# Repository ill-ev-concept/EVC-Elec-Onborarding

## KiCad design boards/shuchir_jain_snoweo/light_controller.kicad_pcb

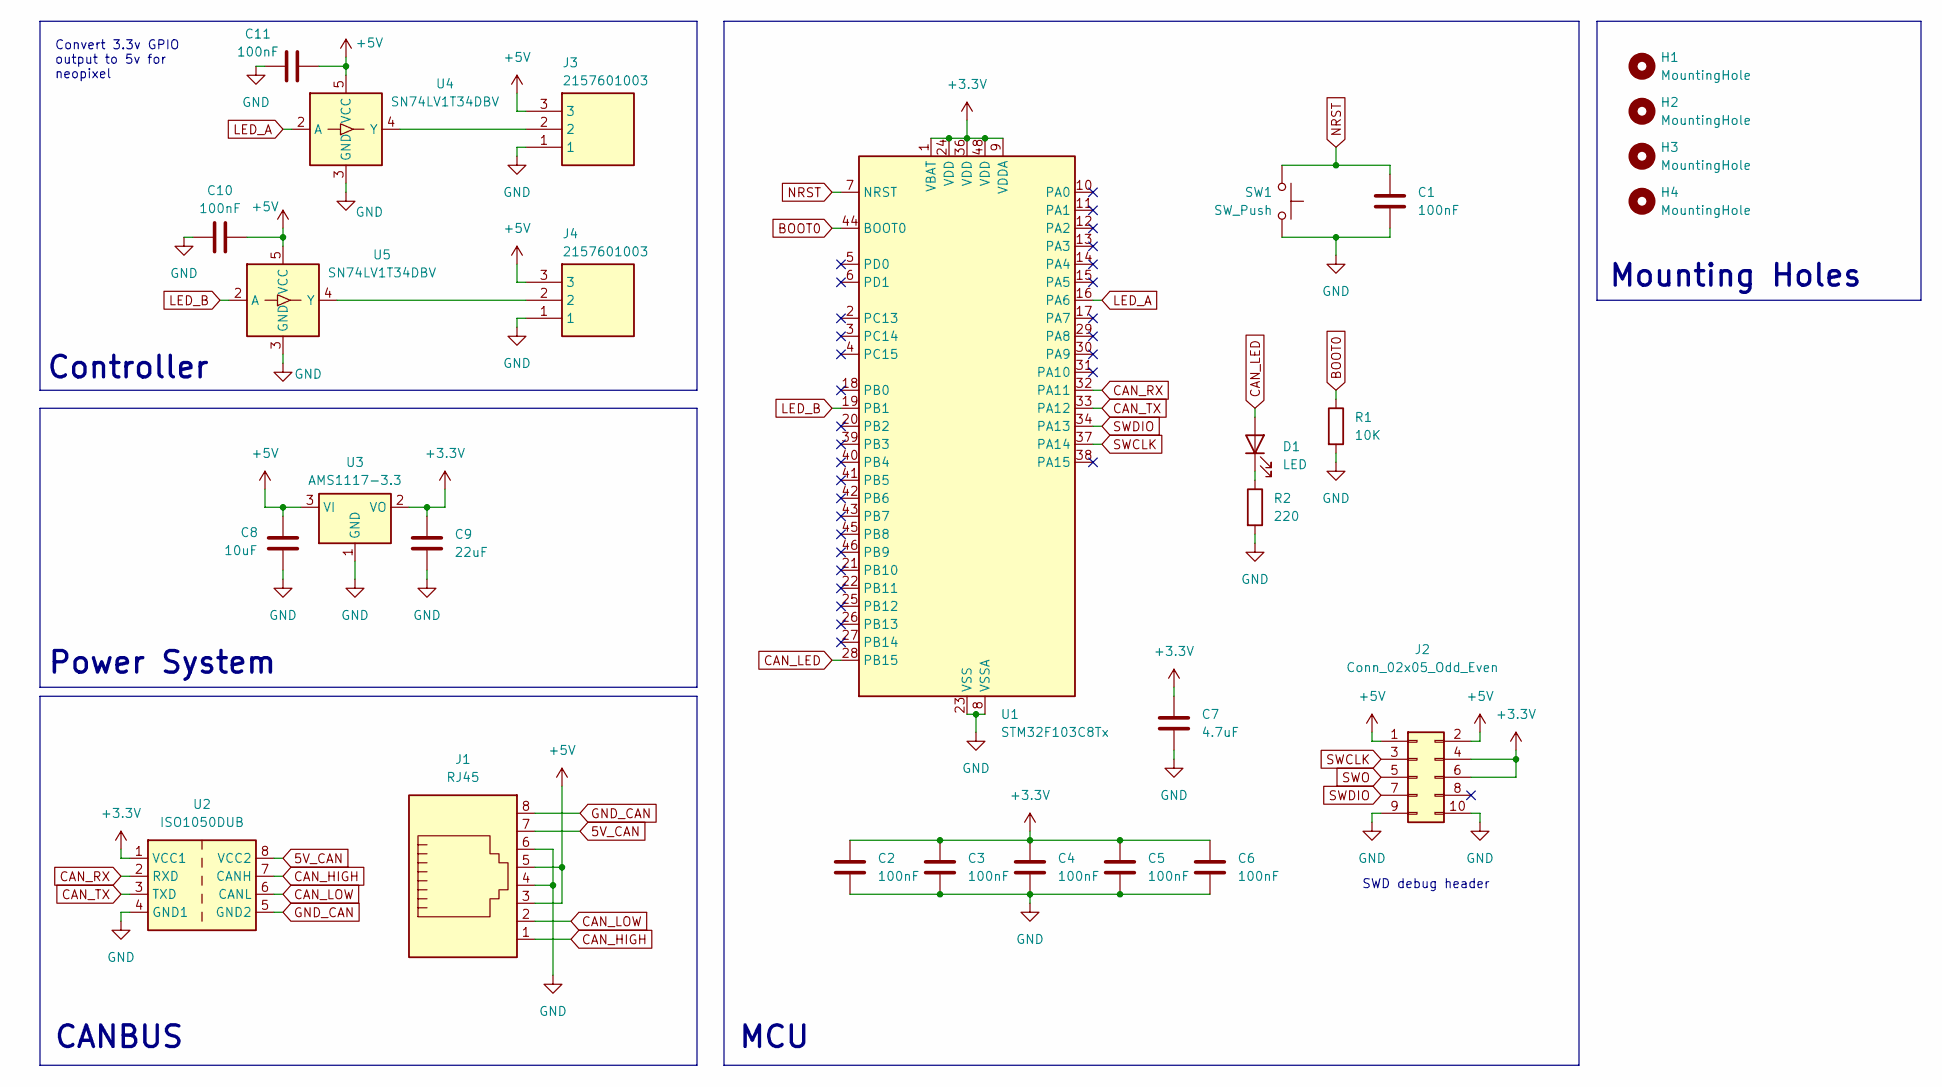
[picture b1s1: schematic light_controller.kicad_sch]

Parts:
C1, C2, C3, C4, C5, C6, C10, C11: 100nF; C_0805_2012Metric
C7: 4.7uF; C_0805_2012Metric
C8: 10uF; C_0805_2012Metric
C9: 22uF; C_0805_2012Metric
D1: LED; LED_0805_2012Metric
H1, H2, H3, H4: MountingHole; MountingHole_3.2mm_M3
J1: RJ45; RJ45_BEL_SS74301-00x_Vertical
J2: Conn_02x05_Odd_Even; PinHeader_2x05_P2.54mm_Vertical_SMD
J3, J4: 2157601003; 215760YY03; Manufacturer_Part_Number 2157601003
R1: 10K; R_0805_2012Metric
R2: 220; R_0805_2012Metric
SW1: SW_Push; SW_SPST_EVQQ2
U1: STM32F103C8Tx; LQFP-48_7x7mm_P0.5mm
U2: ISO1050DUB; SOP-8_6.62x9.15mm_P2.54mm
U3: AMS1117-3.3; SOT-223-3_TabPin2
U4, U5: SN74LV1T34DBV; SOT-23-5

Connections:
5V_CAN: J1.7, U2.8 (VCC2)
+3.3V: C2.1, C3.1, C4.1, C5.1, C6.1, C7.1, C9.1, J2.4, J2.6, U1.1 (VBAT), U1.9 (VDDA), U1.24 (VDD), U1.36 (VDD), U1.48 (VDD), U2.1 (VCC1), U3.2 (VO)
+5V: C8.1, C10.2, C11.2, J1.3, J1.5, J2.1, J2.2, J3.3, J4.3, U3.3 (VI), U4.5 (VCC), U5.5 (VCC)
BOOT0: R1.1, U1.44 (BOOT0)
CAN_HIGH: J1.1, U2.7 (CANH)
CAN_LED: D1.2 (A), U1.28 (PB15)
CAN_LOW: J1.2, U2.6 (CANL)
CAN_RX: U1.32 (PA11), U2.2 (RXD)
CAN_TX: U1.33 (PA12), U2.3 (TXD)
GND: C1.2, C2.2, C3.2, C4.2, C5.2, C6.2, C7.2, C8.2, C9.2, C10.1, C11.1, J1.4, J1.6, J2.9, J2.10, J3.1, J4.1, R1.2, R2.2, SW1.1, U1.8 (VSSA), U1.23 (VSS), U1.35 (VSS), U1.47 (VSS), U2.4 (GND1), U3.1 (GND), U4.3 (GND), U5.3 (GND)
GND_CAN: J1.8, U2.5 (GND2)
LED_A: U1.16 (PA6), U4.2 (A)
LED_B: U1.19 (PB1), U5.2 (A)
NRST: C1.1, SW1.2, U1.7 (NRST)
unnamed: D1.1 (K), R2.1
unnamed: J3.2, U4.4 (Y)
unnamed: J4.2, U5.4 (Y)
SWCLK: J2.3, U1.37 (PA14)
SWDIO: J2.7, U1.34 (PA13)
SWO: J2.5

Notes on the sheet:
Convert 3.3v GPIO output to 5v for neopixel
Power System
Mounting Holes
MCU
SWD debug header
CANBUS
Controller

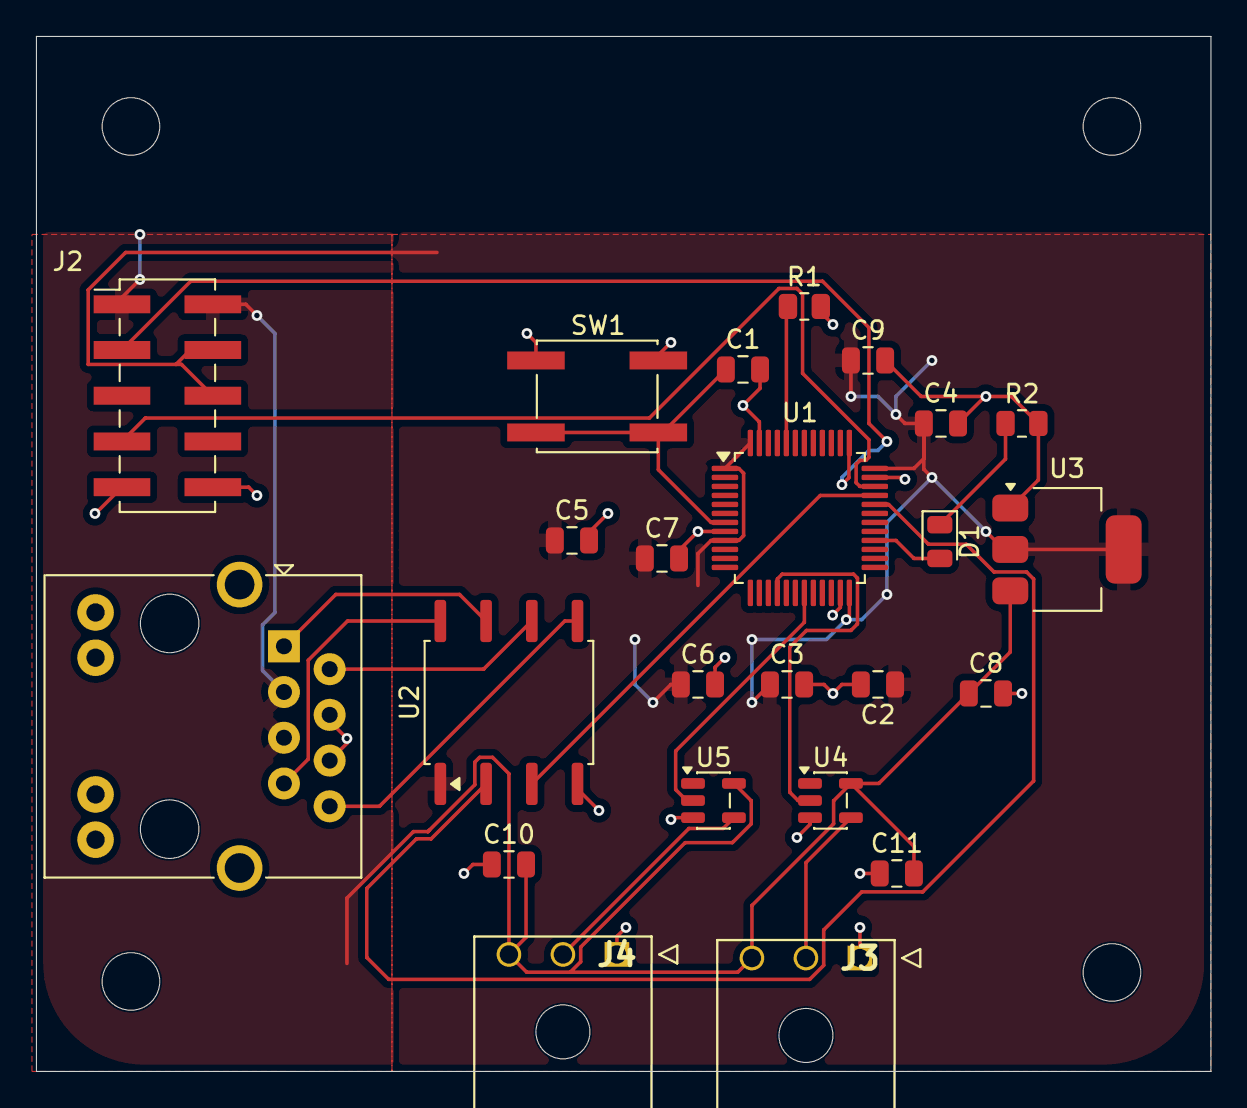
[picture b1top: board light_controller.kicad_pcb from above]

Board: 2 copper layers, 65.2 x 57.5 mm, 28 parts (0 on the bottom side), 19 nets.

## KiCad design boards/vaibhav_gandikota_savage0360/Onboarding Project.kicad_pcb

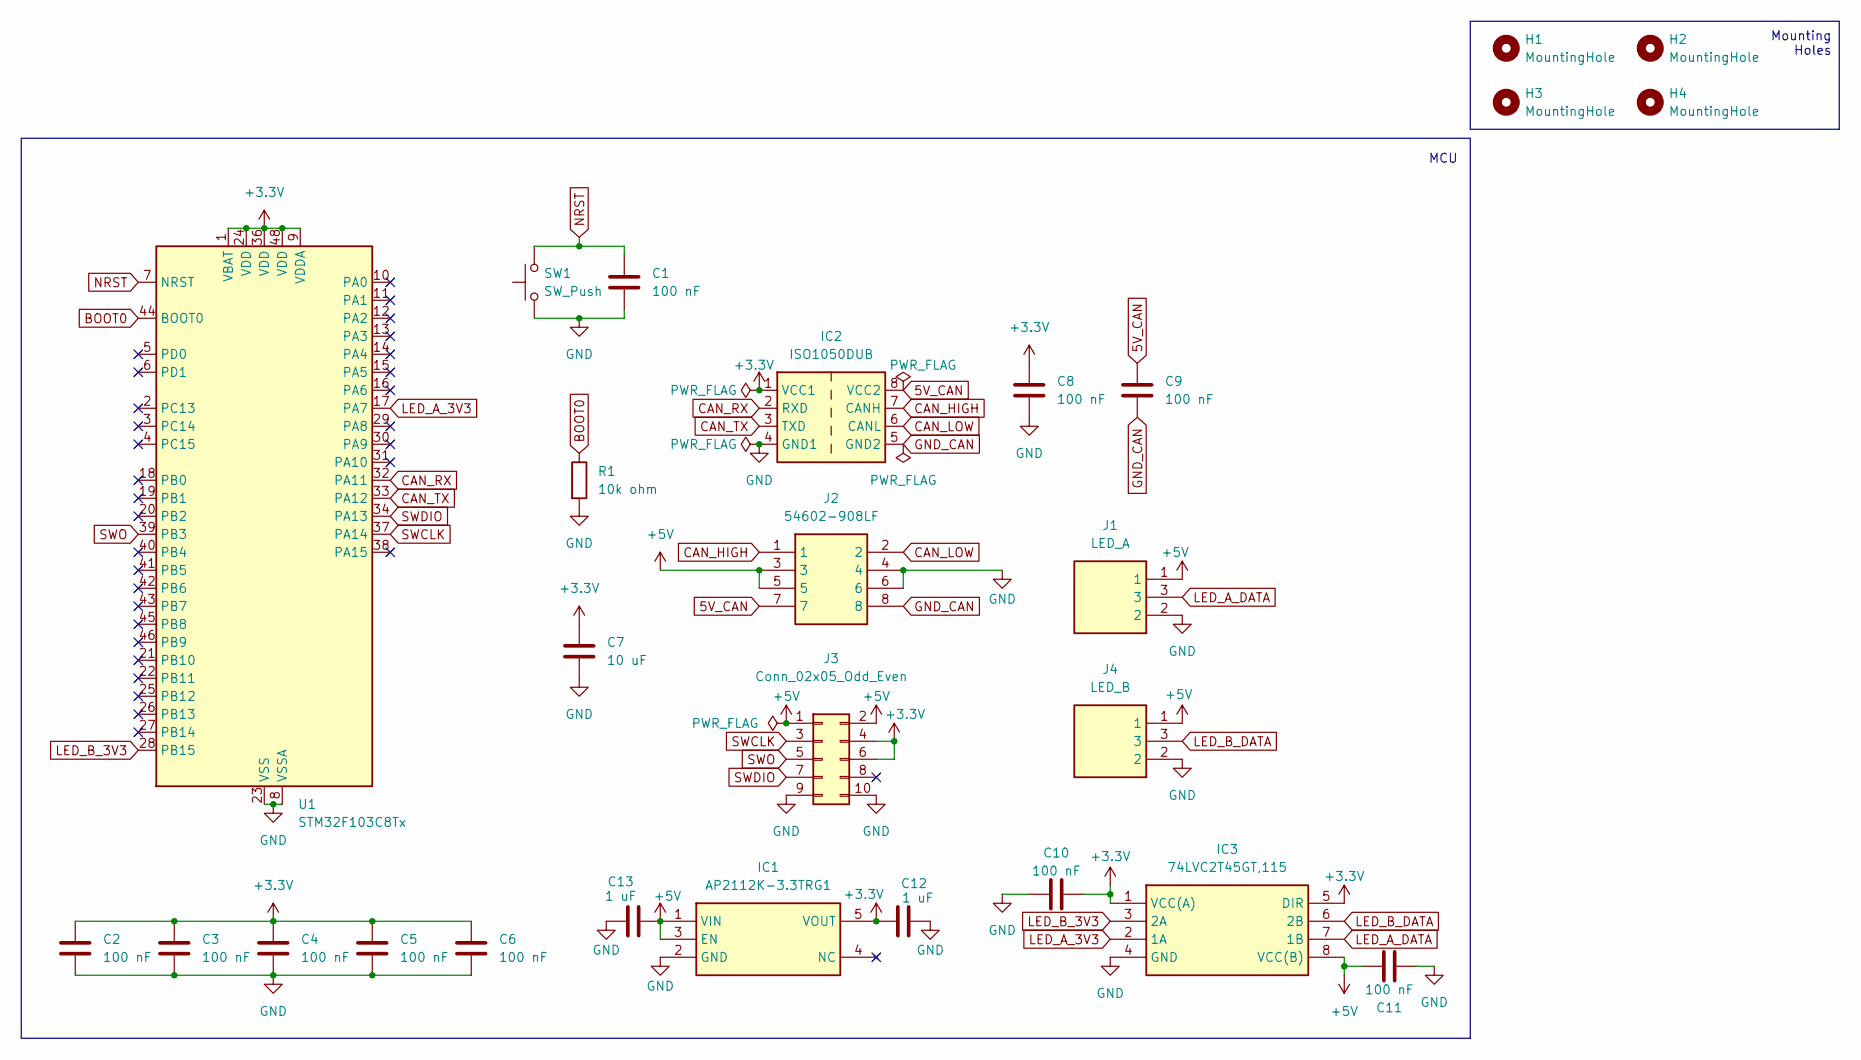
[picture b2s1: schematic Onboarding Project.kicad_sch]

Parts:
C1, C2, C3, C4, C5, C6, C8, C9, C10, C11: 100 nF; C_0805_2012Metric
C7: 10 uF; C_0805_2012Metric
C12, C13: 1 uF; C_0805_2012Metric
H1, H2, H3, H4: MountingHole; MountingHole_4.3mm_M4
IC1: AP2112K-3.3TRG1; SOT95P285X140-5N; Manufacturer_Part_Number AP2112K-3.3TRG1; Mouser Part Number 621-AP2112K-3.3TRG1
IC2: ISO1050DUB; SOP-8_6.62x9.15mm_P2.54mm
IC3: 74LVC2T45GT,115; 74AVC9112GTX; Manufacturer_Part_Number 74LVC2T45GT,115; Mouser Part Number 771-74LVC2T45GT115
J1: LED_A; 215760YY03; Manufacturer_Part_Number 2157601003
J2: 54602-908LF; 54602908LF; Manufacturer_Part_Number 54602-908LF
J3: Conn_02x05_Odd_Even; PinSocket_2x05_P2.54mm_Vertical
J4: LED_B; 215760YY03; Manufacturer_Part_Number 2157601003
R1: 10k ohm; R_0805_2012Metric
SW1: SW_Push; SW_SPST_EVQQ2
U1: STM32F103C8Tx; LQFP-48_7x7mm_P0.5mm

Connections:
5V_CAN: C9.1, IC2.8 (VCC2), J2.7
+3.3V: C2.1, C3.1, C4.1, C5.1, C6.1, C7.1, C8.1, C10.2, C12.1, IC1.5 (VOUT), IC2.1 (VCC1), IC3.1 (VCC(A)), IC3.5 (DIR), J3.4, J3.6, U1.1 (VBAT), U1.9 (VDDA), U1.24 (VDD), U1.36 (VDD), U1.48 (VDD)
+5V: C11.2, C13.2, IC1.1 (VIN), IC1.3 (EN), IC3.8 (VCC(B)), J1.1, J2.3, J2.5, J3.1, J3.2, J4.1
BOOT0: R1.1, U1.44 (BOOT0)
CAN_HIGH: IC2.7 (CANH), J2.1
CAN_LOW: IC2.6 (CANL), J2.2
CAN_RX: IC2.2 (RXD), U1.32 (PA11)
CAN_TX: IC2.3 (TXD), U1.33 (PA12)
GND: C1.2, C2.2, C3.2, C4.2, C5.2, C6.2, C7.2, C8.2, C10.1, C11.1, C12.2, C13.1, IC1.2 (GND), IC2.4 (GND1), IC3.4 (GND), J1.2, J2.4, J2.6, J3.9, J3.10, J4.2, R1.2, SW1.1, U1.8 (VSSA), U1.23 (VSS), U1.35 (VSS), U1.47 (VSS)
GND_CAN: C9.2, IC2.5 (GND2), J2.8
LED_A_3V3: IC3.2 (1A), U1.17 (PA7)
LED_A_DATA: IC3.7 (1B), J1.3
LED_B_3V3: IC3.3 (2A), U1.28 (PB15)
LED_B_DATA: IC3.6 (2B), J4.3
NRST: C1.1, SW1.2, U1.7 (NRST)
SWCLK: J3.3, U1.37 (PA14)
SWDIO: J3.7, U1.34 (PA13)
SWO: J3.5, U1.39 (PB3)

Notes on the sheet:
Mounting Holes
MCU

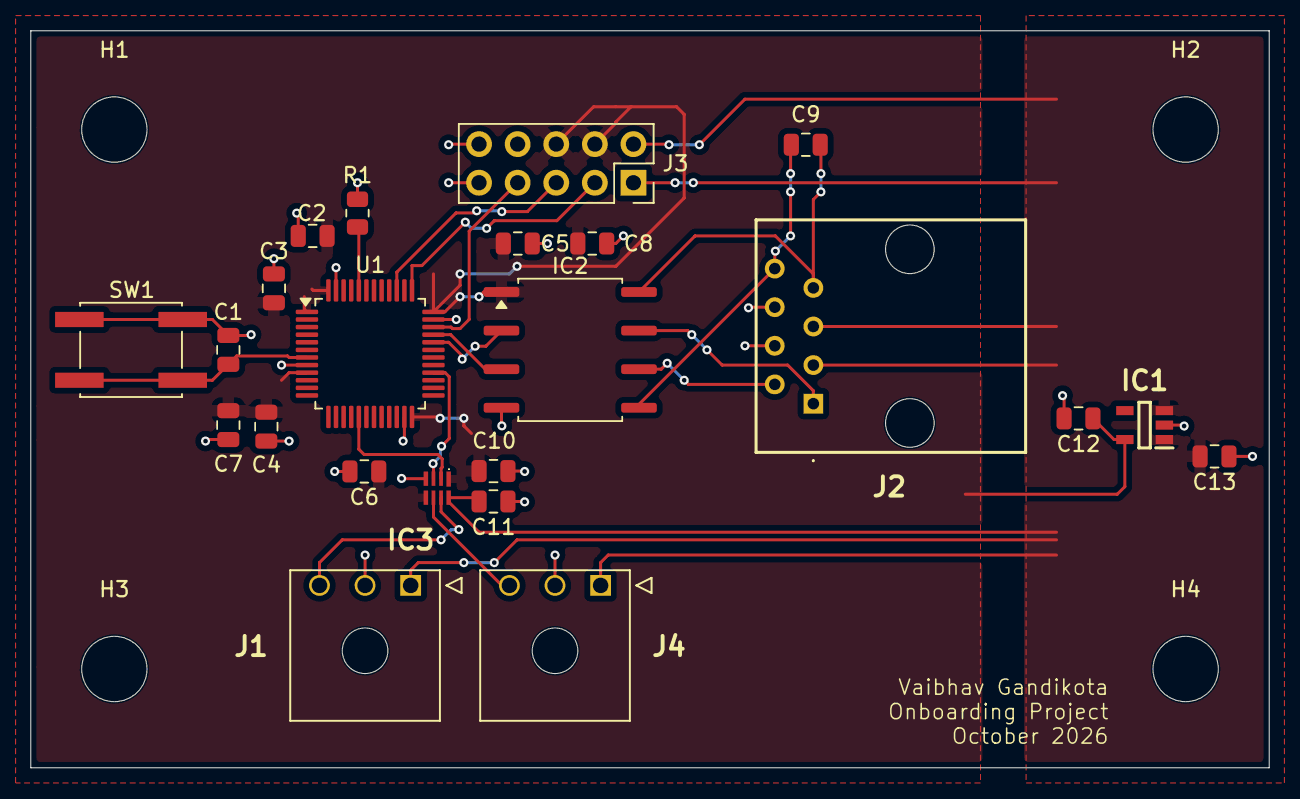
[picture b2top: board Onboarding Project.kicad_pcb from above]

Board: 2 copper layers, 81.5 x 48.5 mm, 27 parts (0 on the bottom side), 18 nets.

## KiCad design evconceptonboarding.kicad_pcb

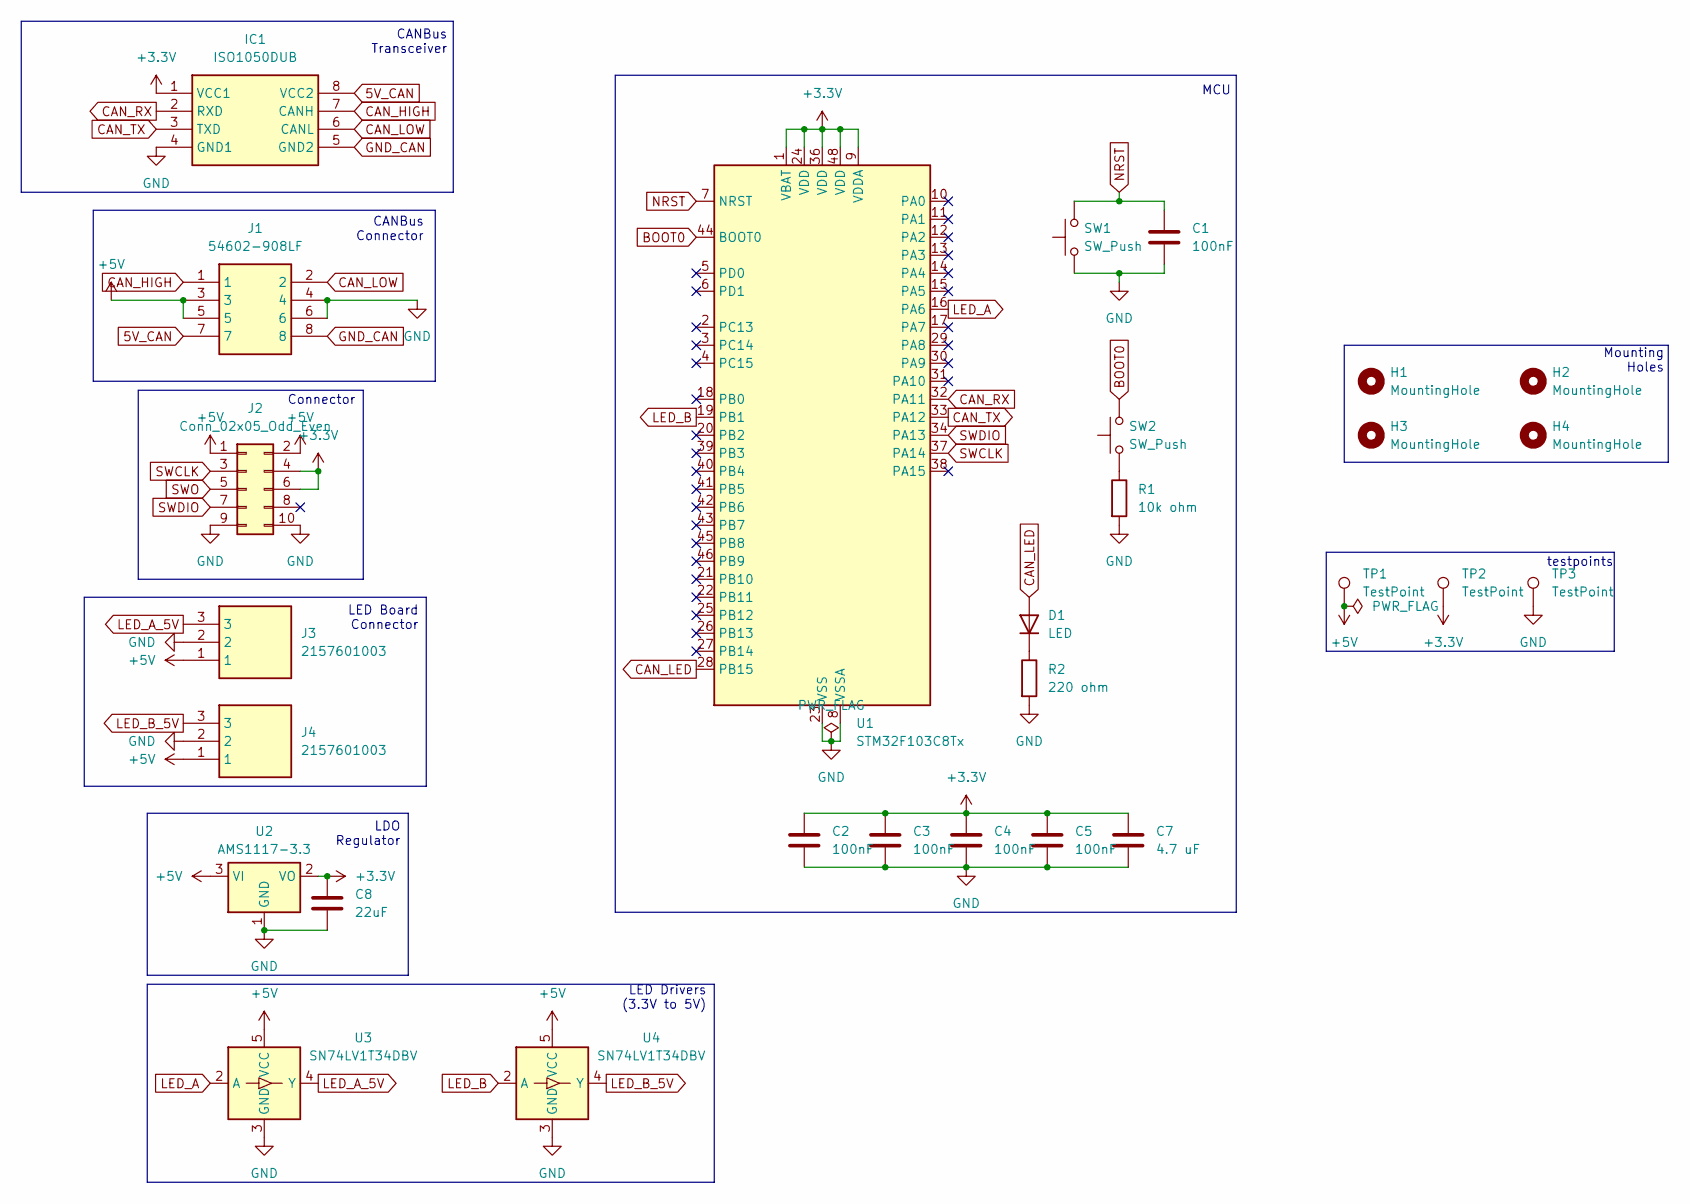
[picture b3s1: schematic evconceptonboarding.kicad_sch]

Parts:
C1, C2, C3, C4, C5: 100nF; C_0805_2012Metric
C7: 4.7 uF; C_0805_2012Metric
C8: 22uF; C_0805_2012Metric
D1: LED; LED_0805_2012Metric
H1, H2, H3, H4: MountingHole; MountingHole_3.2mm_M3
IC1: ISO1050DUB; SOP254P1040X485-8N; Manufacturer_Part_Number ISO1050DUB; Mouser Part Number 595-ISO1050DUB
J1: 54602-908LF; 54602908LF; Manufacturer_Part_Number 54602-908LF
J2: Conn_02x05_Odd_Even; PinSocket_2x05_P2.54mm_Vertical
J3, J4: 2157601003; 215760YY03; Manufacturer_Part_Number 2157601003
R1: 10k ohm; R_0805_2012Metric
R2: 220 ohm; R_0805_2012Metric
SW1, SW2: SW_Push; SW_SPST_EVQQ2
TP1, TP2, TP3: TestPoint; TestPoint_Bridge_Pitch2.54mm_Drill0.7mm
U1: STM32F103C8Tx; LQFP-48_7x7mm_P0.5mm
U2: AMS1117-3.3; SOT-223-3_TabPin2
U3, U4: SN74LV1T34DBV; SOT-23-5

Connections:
5V_CAN: IC1.8 (VCC2), J1.7
+3.3V: C2.1, C3.1, C4.1, C5.1, C7.1, C8.1, IC1.1 (VCC1), J2.4, J2.6, TP2.1 (1_1), U1.1 (VBAT), U1.9 (VDDA), U1.24 (VDD), U1.36 (VDD), U1.48 (VDD), U2.2 (VO)
+5V: J1.3, J1.5, J2.1, J2.2, J3.1, J4.1, TP1.1 (1_1), U2.3 (VI), U3.5 (VCC), U4.5 (VCC)
BOOT0: SW2.2, U1.44 (BOOT0)
CAN_HIGH: IC1.7 (CANH), J1.1
CAN_LED: D1.2 (A), U1.28 (PB15)
CAN_LOW: IC1.6 (CANL), J1.2
CAN_RX: IC1.2 (RXD), U1.32 (PA11)
CAN_TX: IC1.3 (TXD), U1.33 (PA12)
GND: C1.2, C2.2, C3.2, C4.2, C5.2, C7.2, C8.2, IC1.4 (GND1), J1.4, J1.6, J2.9, J2.10, J3.2, J4.2, R1.2, R2.2, SW1.1, TP3.1 (1_1), U1.8 (VSSA), U1.23 (VSS), U1.35 (VSS), U1.47 (VSS), U2.1 (GND), U3.3 (GND), U4.3 (GND)
GND_CAN: IC1.5 (GND2), J1.8
LED_A: U1.16 (PA6), U3.2 (A)
LED_A_5V: J3.3, U3.4 (Y)
LED_B: U1.19 (PB1), U4.2 (A)
LED_B_5V: J4.3, U4.4 (Y)
NRST: C1.1, SW1.2, U1.7 (NRST)
unnamed: D1.1 (K), R2.1
unnamed: R1.1, SW2.1
SWCLK: J2.3, U1.37 (PA14)
SWDIO: J2.7, U1.34 (PA13)
SWO: J2.5

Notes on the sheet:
LDO Regulator
MCU
Mounting Holes
Connector
testpoints
LED Drivers (3.3V to 5V)
CANBus Connector
LED Board Connector
CANBus Transceiver

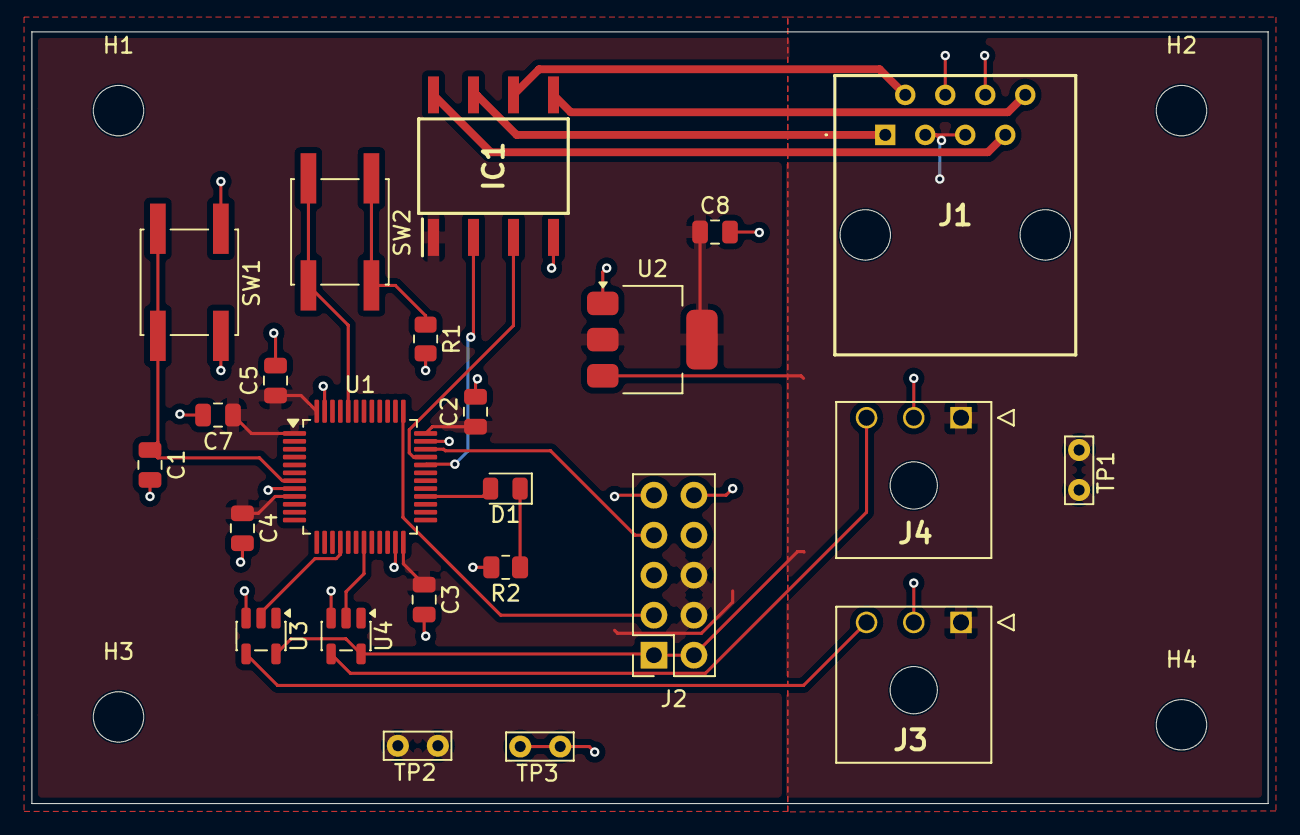
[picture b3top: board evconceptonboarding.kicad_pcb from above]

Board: 2 copper layers, 78.5 x 49.0 mm, 28 parts (0 on the bottom side), 20 nets.

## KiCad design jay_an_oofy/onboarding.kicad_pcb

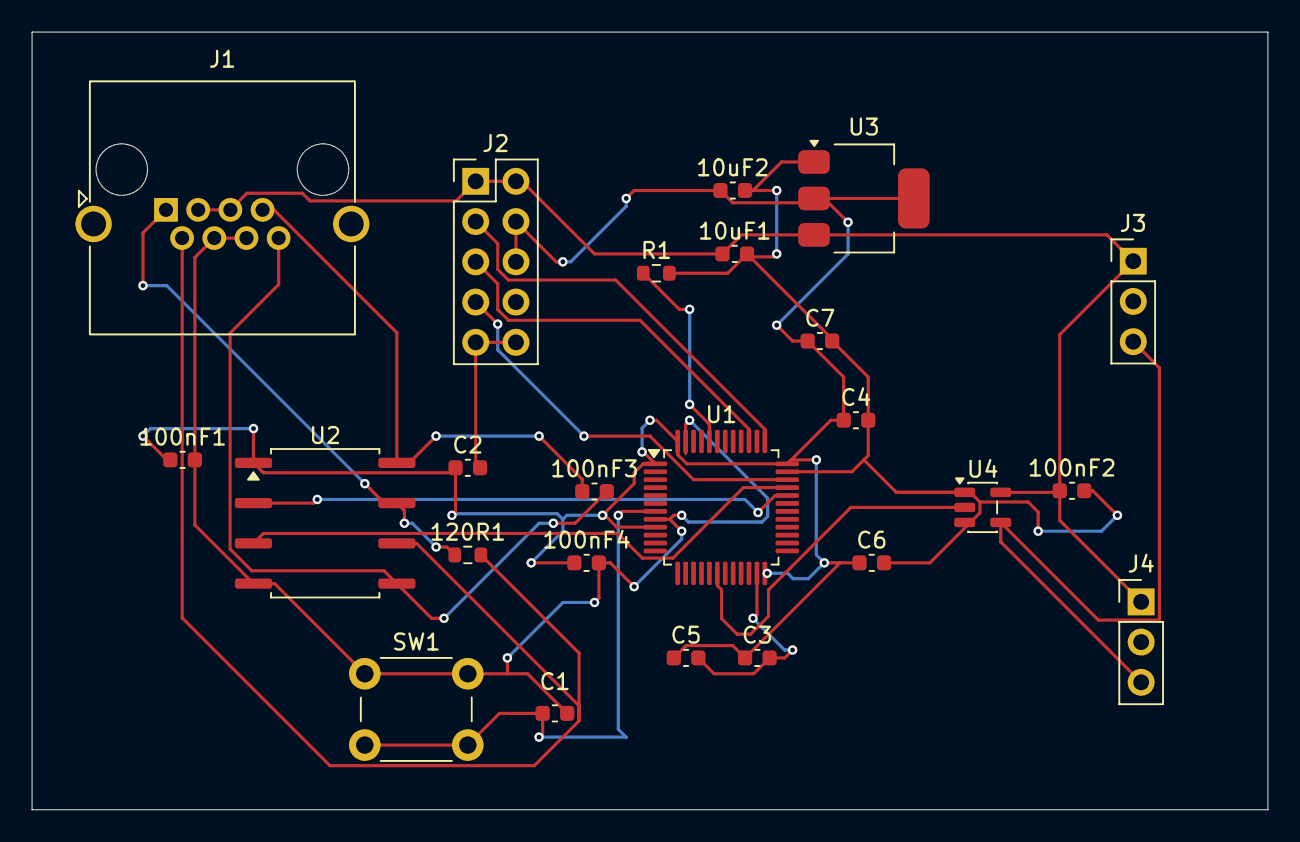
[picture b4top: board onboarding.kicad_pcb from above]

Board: 2 copper layers, 78.0 x 49.1 mm, 24 parts (0 on the bottom side), 16 nets.

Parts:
10uF1, 10uF2, 100nF1, 100nF2, 100nF4: C_0603_1608Metric
100nF3: C; C_0603_1608Metric
120R1: 120; R_0603_1608Metric
C1, C2, C3, C4, C5, C6: 100nF; C_0603_1608Metric
C7: 4.7uF; C_0603_1608Metric
J1: RJ45; RJ45_Amphenol_RJHSE5380
J2: Conn_02x05_Odd_Even; PinHeader_2x05_P2.54mm_Vertical
J3, J4: Conn_01x03_Pin; PinHeader_1x03_P2.54mm_Vertical
R1: 10kR; R_0603_1608Metric
SW1: SW_Push; SW_PUSH_6mm
U1: STM32F103C8Tx; LQFP-48_7x7mm_P0.5mm
U2: ISO1050DUB; SOP-8_6.62x9.15mm_P2.54mm
U3: AMS1117-3.3; SOT-223-3_TabPin2
U4: 74AHCT1G125; SOT-23-5

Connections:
5VCAN: 100nF3.1, J1.7, U2.8 (VCC2)
+3.3V: 10uF2.1, 100nF1.1, 100nF4.1, C2.1, C3.1, C4.1, C5.1, C6.1, C7.1, J2.4, J2.6, U1.1 (VBAT), U1.9 (VDDA), U1.24 (VDD), U1.36 (VDD), U1.48 (VDD), U2.1 (VCC1), U3.2 (VO)
+5V: 10uF1.1, 100nF2.1, J1.3, J1.5, J2.1, J2.2, J3.1, J4.1, U3.3 (VI), U4.5 (VCC)
BOOTO: R1.1, U1.44 (BOOT0)
CAN_HIGH: 120R1.1, J1.1, U2.7 (CANH)
CAN_LOW: 120R1.2, J1.2, U2.6 (CANL)
CAN_RX: U1.32 (PA11), U2.2 (RXD)
CAN_TX: U1.33 (PA12), U2.3 (TXD)
GND: 10uF1.2, 10uF2.2, 100nF1.2, 100nF2.2, 100nF4.2, C1.2, C2.2, C3.2, C4.2, C5.2, C6.2, C7.2, J1.4, J1.6, J2.9, J2.10, J3.2, J4.2, R1.2, SW1.1, U1.8 (VSSA), U1.23 (VSS), U1.35 (VSS), U1.47 (VSS), U2.4 (GND1), U3.1 (GND), U4.1, U4.3 (GND)
GNDCAN: 100nF3.2, J1.8, U2.5 (GND2)
LED_DATA_3V: U1.18 (PB0), U4.2
LED_DATA_5V: J3.3, J4.3, U4.4
NRST: C1.1, SW1.2, U1.7 (NRST)
SWCLK: J2.3, U1.37 (PA14)
SWDIO: J2.7, U1.34 (PA13)
SWO: J2.5, U1.39 (PB3)
